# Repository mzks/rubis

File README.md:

# rubis

ADC board for 16 channels Slow Control on Raspberry pi.
This repository provides board design and control software.

## Demo
 - 30 seconds to start

 - Web watching demo

It is easy to watch your sensors with rubis + Grafana

 - PCB view on Raspbery Pi

## Feature

 - Standalone
 - Inexpensive
 - Multi channels (16 ch) and additional connectors (4 ch)
 - Including CLI software (This!)

## Hardware components
 - rubis board - less than 5 dollars at elecrow 
 - Raspberry Pi (1B+, 2B, 3B, 3B+, 4B, Zero)
 - [PIN Socket](https://akizukidenshi.com/catalog/g/gC-00085/) 
 - [ADC Board](https://www.marutsu.co.jp/pc/i/574270/) * 1--4 / 20 dollers per board
 - [BNC Connector](https://akizukidenshi.com/catalog/g/gC-00134/) ( * 4, optional)
 - [SMA Connector](https://akizukidenshi.com/catalog/g/gC-02569/) ( * 4, optional)
 - LEMO Connector (Optional)

## Hardware

You need to connect the four GPIO pins arranged in a square (Pin 3 -- SDA, Pin 4 -- 5V, Pin 5 -- SCL, Pin 6 -- GND).
 - [Circuit diagram](https://github.com/mzks/rubis/blob/main/hardware/rubis_circuit.pdf)
 - [3D view](https://github.com/mzks/rubis/blob/main/hardware/rubis.step)
 - [KiCad files](https://github.com/mzks/rubis/blob/main/hardware)

## Software

### Install
Before run, enable I2C on Raspberry Pi. (`sudo raspi-config`)
Then, you can find the i2c devices like this.
```
> sudo i2cdetect -y 1
     0  1  2  3  4  5  6  7  8  9  a  b  c  d  e  f
00:          -- -- -- -- -- -- -- -- -- -- -- -- --
10: -- -- -- -- -- -- -- -- -- -- -- -- -- -- -- --
20: -- -- -- -- -- -- -- -- -- -- -- -- -- -- -- --
30: -- -- -- -- -- -- -- -- -- -- -- -- -- -- -- --
40: -- -- -- -- -- -- -- -- 48 49 4a 4b -- -- -- --
50: -- -- -- -- -- -- -- -- -- -- -- -- -- -- -- --
60: -- -- -- -- -- -- -- -- -- -- -- -- -- -- -- --
70: -- -- -- -- -- -- -- --
```
If you will use an old raspberry pi, run `sudo apt install libatlas-base-dev` to use `numpy` (This tool doesn't depend on `numpy`).

Then, type `pip3 install rubis`
The `rubis` binary will be provided at `~/.local/bin/rubis`
You want mysql store, please see `Database setting` below.

### Usage
When you execute `rubis` without option, logging immidiately starts with default configurations.
You can use your custom configuration file with `-c` option.

`rubis -g` generates template config file.
Edit them, then run `rubis -c custom_config.json`.
At the **strong** request of the author's supervisor, the following commands are available to people in CYGNUS (dark matter search experiment) without creating or editing a new configuration file.
```
rubis -c cygnus
```
In addition of `cygnus`, `one_board` and `mysql` configurations are pre-defined.

Some configurations can be overwrited with command line options.
`rubis -h` provides option descriptions.
The output file format is CSV/MySQL.

As a default, the csv files like `sc-20211029-75enrt.csv` are created.
The `75enrt` is a unique hash created by configurations.
The hash helps separation not to mix files taken with different configurations.
The CSV format is like that.
```
time,ch1,ch2,ch3,ch4,ch5,ch6,ch7,ch8,ch9,ch10,ch11,ch12,ch13,ch14,ch15,ch16
2021-10-29 00:49:50, 0.5481417, 0.5476417, 0.5483917, 0.5476417, 0.5432666, 0.5430166, 0.5441416, 0.5433916, 0.5486417, 0.5478917, 0.5482667, 0.5477667, 0.5441416, 0.5446416, 0.5440166, 0.5440166
2021-10-29 00:50:51, 0.5486417, 0.5483917, 0.5475167, 0.5476417, 0.5437666, 0.5435166, 0.5435166, 0.5436416, 0.5482667, 0.5483917, 0.5485167, 0.5481417, 0.5451416, 0.5451416, 0.5438916, 0.5437666
2021-10-29 00:51:51, 0.5480167, 0.5478917, 0.5480167, 0.5475167, 0.5432666, 0.5431416, 0.5430166, 0.5437666, 0.5482667, 0.5481417, 0.5481417, 0.5480167, 0.5445166, 0.5436416, 0.5443916, 0.5443916
2021-10-29 00:52:51, 0.5487667, 0.5481417, 0.5481417, 0.5481417, 0.5437666, 0.5437666, 0.5438916, 0.5435166, 0.5487667, 0.5482667, 0.5483917, 0.5478917, 0.5448916, 0.5440166, 0.5442666, 0.5438916
2021-10-29 00:53:52, 0.5482667, 0.5486417, 0.5476417, 0.5477667, 0.5438916, 0.5437666, 0.5432666, 0.5435166, 0.5487667, 0.5481417, 0.5481417, 0.5485167, 0.5445166, 0.5440166, 0.5441416, 0.5440166
2021-10-29 00:54:52, 0.5482667, 0.5478917, 0.5477667, 0.5478917, 0.5433916, 0.5430166, 0.5436416, 0.5438916, 0.5487667, 0.5487667, 0.5488918, 0.5478917, 0.5451416, 0.5447666, 0.5442666, 0.5441416
2021-10-29 00:55:53, 0.5487667, 0.5480167, 0.5478917, 0.5475167, 0.5441416, 0.5437666, 0.5435166, 0.5433916, 0.5487667, 0.5480167, 0.5483917, 0.5482667, 0.5452666, 0.5450166, 0.5448916, 0.5441416
2021-10-29 00:56:53, 0.5487667, 0.5483917, 0.5482667, 0.5481417, 0.5440166, 0.5438916, 0.5441416, 0.5443916, 0.5491418, 0.5487667, 0.5483917, 0.5482667, 0.5446416, 0.5442666, 0.5441416, 0.5445166
2021-10-29 00:57:54, 0.5478917, 0.5483917, 0.5480167, 0.5480167, 0.5441416, 0.5438916, 0.5440166, 0.5442666, 0.5491418, 0.5488918, 0.5488918, 0.5481417, 0.5450166, 0.5443916, 0.5441416, 0.5442666
```

The `-r` option makes "dry-run".
With the option, this rubis works on general system not raspberry pi even without ADS board.
It helps to know how rubis works.

The `-l` option show rubis log.
It helps to find the logfile place and configuration with hash.

If you miss a config to generate hash, `-b` option helps you.
`rubis -b g2hlpc` generates the config file run before.

The `-q` option kill all rubis processes.
With the `-s` option, rubis uses the stored cofiguration used in the previous run.

For analysis with pandas dataframe, it is easy to extract the csv files.
```
import pandas as pd
from glob import glob

hash_str = '75enrt'
df = [pd.read_csv(name, parse_dates=[0], index_col=0) for name in sorted(glob('./*'+hash_str+'.csv'))]
df = pd.concat(df)
```

### Config option

| Configure name      | Description                      | Option                                                          | Overwrite option |
| ------------------- | -------------------------------- | --------------------------------------------------------------- | ---------------- |
| `path`              | Path to store the data           | Default: "./"                                                   | -p               |
| `file_header`       | File header of generated file    | Default: "sc"                                                   | -f               |
| `naming`            | Naming style of file             | `'date_hash.csv'`, etc. Available keywords : 'head', 'date', 'id', 'hash', 'host' | -n               |
| `rubis_id`          | rubis id (string)                | Used to identify your rubis board                               | -i               |
| `time_interval_sec` | Data taking time interval (sec)  | Default: 10                                                     | -t               |
| `available_boards`  | List of available ADS1115 boards | Default: [1,2,3,4]                                              | -a               |
| `output`            | Output format                    | `"csv"`, `"db"`, or `"both"`                                    | -o               |
| `delimiter`         | Delimiter for csv output         | `","`, `" "`, `"space"`, etc.                                          | -d               |
| `commentout_string` | Strings to be added on the csv file header | default: ""                                           |                  |
| `time_format`       | Time column format               | "timestamp", "datetime" (default), or strftime format (for example, "%H:%M:%S") |  |
| `boards`            | Setting for each ADS1115 board   | `"gain"` option is available                                    |                  |
| `sources`           | Setting for each channels        |                                                                 |                  |

If you select `naming` including "date", a new file will be created day by day.

The sources should be set like,
```
"1":{
    "name": "ch1",
    "description": "channel 1",
    "type": "volt"
    },
"2":{
    "name": "ch2",
    "description": "channel 2",
    "type": "linear"
    "a": 2.0,
    "b": 1.2
    },
```
The `name` is used for csv header. For the `type`, `"volt"`, `"raw"`, `"millivolt"`, and `"linear"` are available.
`"linear"` returns the value `"a" * (volt) + "b"`. The "a" and "b" should be written in the config file, for each sources.

## Database setting
If you want database store, do like that additionaly
```
sudo apt install mariadb-server
sudo mysql -u root
MariaDB [(none)]> UPDATE mysql.user SET password=password('newpassword') WHERE User = 'root';
MariaDB [mysql]> UPDATE mysql.user SET plugin='' WHERE User='root';
MariaDB [mysql]> GRANT ALL PRIVILEGES ON *.* TO 'root'@'localhost' identified by 'newpassword' with grant option;
MariaDB [mysql]> exit
sudo systemctl restart mysql
```
You need an external access, please make a user.
```
CREATE USER 'rubis'@'10.37.%' IDENTIFIED BY 'password';
GRANT ALL ON *.* TO 'rubis'@'10.37.%';
FLUSH PRIVILEGES;
```
And comment out the `bind-address` line in `/etc/mysql/mariadb.conf.d/50-server.cnf`.
In addition, add `default_time_zone='+00:00'` at the bottom of the file.
Then run `sudo systemctl restart mysql`.

If you need static IP access, please edit `/etc/dhcpcd.conf` like this.
```
# Example static IP configuration:
interface eth0
static ip_address=***.***.***.***/** # your IP/mask
static routers=***.***.***.*** # your gateway
static domain_name_servers=***.***.***.*** ***.***.***.*** # your DNS
```

When you set `"db"` or `"both"` for `output` in config file, the following settings are required.
```
"db":{
    "login":{
        "host": "127.0.0.1",
        "port": 3306,
        "user": "root",
        "passwd": "newpassword",
        "autocommit": true},
    "name": "rubis"
    }
```

## For developers
Clone this repository on your machine, then run `make.sh`.
If you need something, please feel free to send a PR or ask me on issue.

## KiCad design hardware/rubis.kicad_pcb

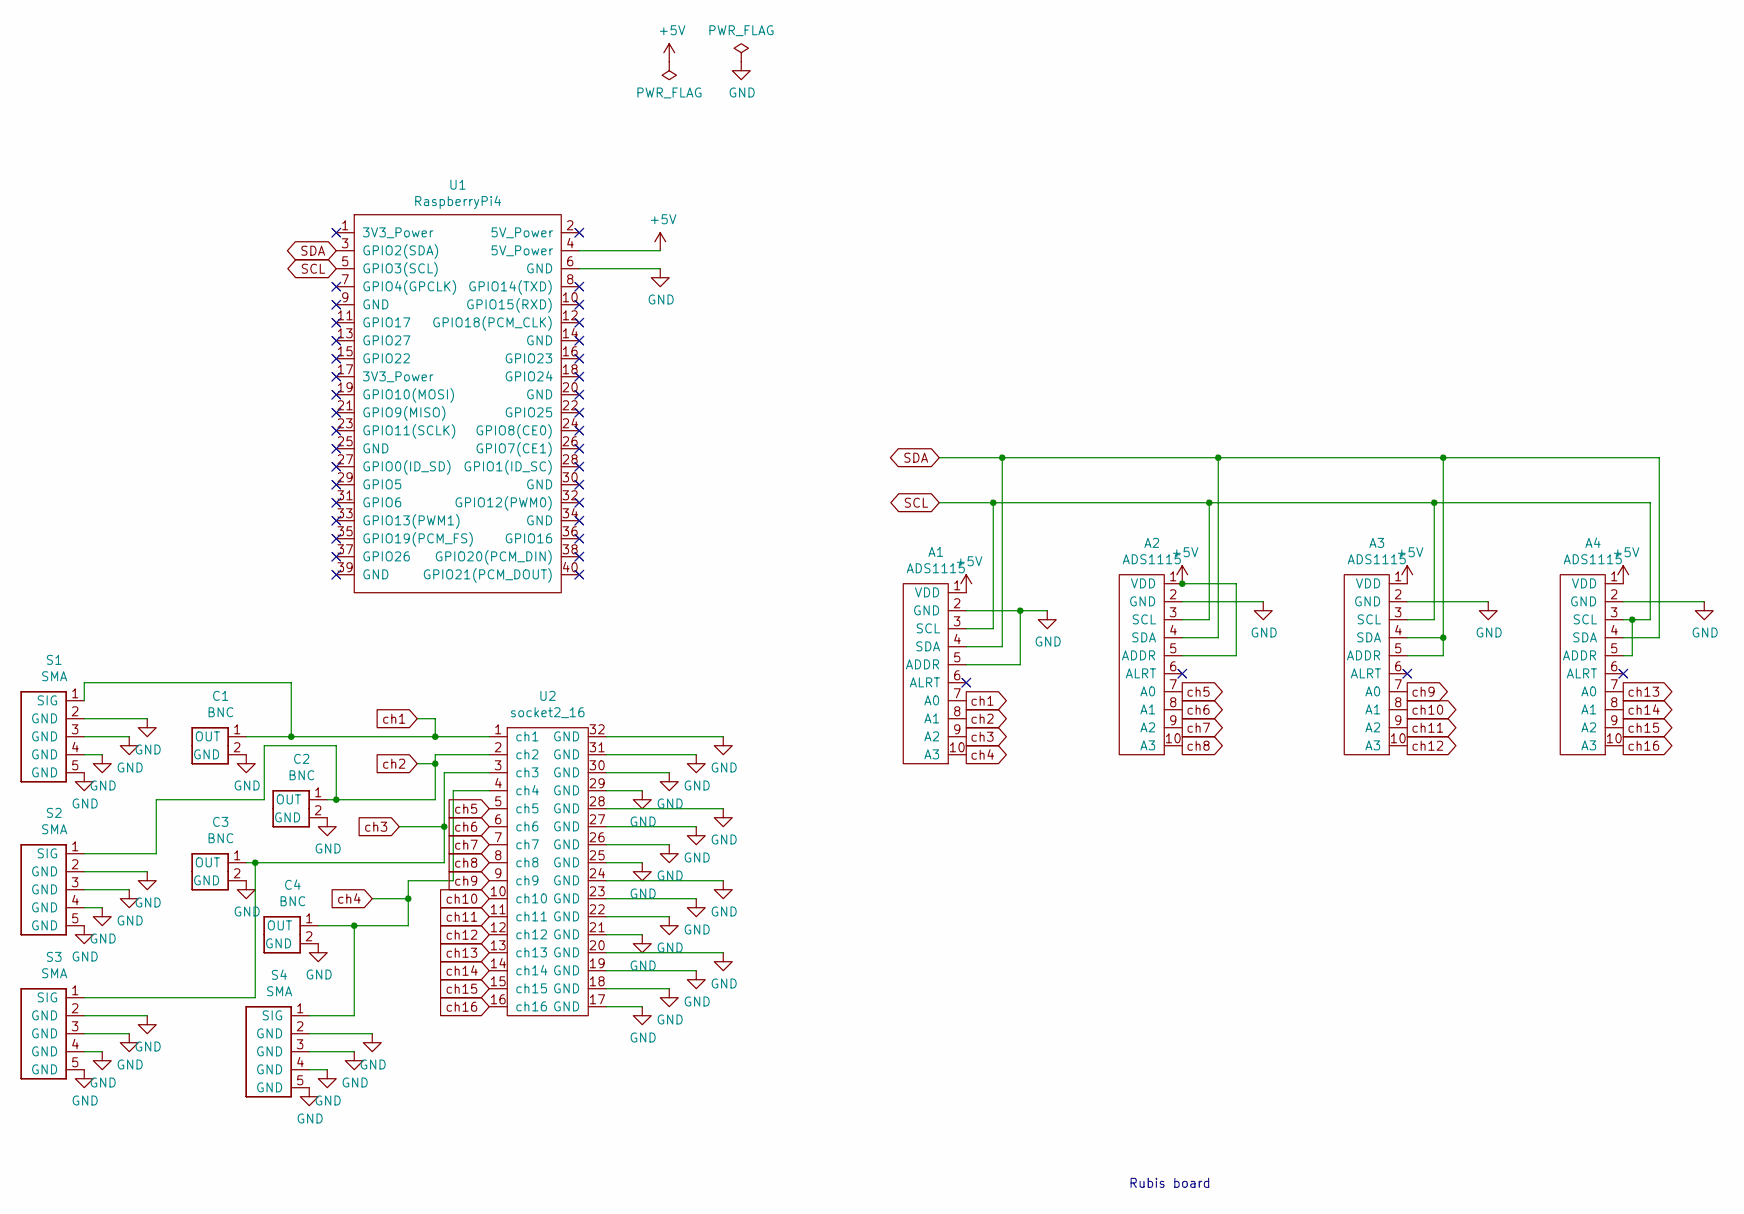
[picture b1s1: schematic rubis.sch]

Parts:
A1, A2, A3, A4: ADS1115; ads1115
C1, C2, C3, C4: BNC
S1, S2, S3, S4: SMA
U1: RaspberryPi4; rasp_40pin
U2: socket2_16; 2_16_socket

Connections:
+5V: A1.1 (VDD), A2.1 (VDD), A2.5 (ADDR), A3.1 (VDD), A4.1 (VDD), U1.4 (5V_Power); also elsewhere on the board
GND: A1.2 (GND), A1.5 (ADDR), A2.2 (GND), A3.2 (GND), A4.2 (GND), C1.2 (GND), C2.2 (GND), C3.2 (GND), C4.2 (GND), S1.2 (GND), S1.3 (GND), S1.4 (GND), S1.5 (GND), S2.2 (GND), S2.3 (GND), S2.4 (GND), S2.5 (GND), S3.2 (GND), S3.3 (GND), S3.4 (GND), S3.5 (GND), S4.2 (GND), S4.3 (GND), S4.4 (GND), S4.5 (GND), U1.6 (GND), U2.17 (GND), U2.18 (GND), U2.19 (GND), U2.20 (GND), U2.21 (GND), U2.22 (GND), U2.23 (GND), U2.24 (GND), U2.25 (GND), U2.26 (GND), U2.27 (GND), U2.28 (GND), U2.29 (GND), U2.30 (GND), U2.31 (GND), U2.32 (GND); also elsewhere on the board
SCL: A1.3 (SCL), A2.3 (SCL), A3.3 (SCL), A4.3 (SCL), A4.5 (ADDR), U1.5 (GPIO3(SCL)); also elsewhere on the board
SDA: A1.4 (SDA), A2.4 (SDA), A3.4 (SDA), A3.5 (ADDR), A4.4 (SDA), U1.3 (GPIO2(SDA)); also elsewhere on the board
ch1: A1.7 (A0), C1.1 (OUT), S1.1 (SIG), U2.1 (ch1); also elsewhere on the board
ch2: A1.8 (A1), C2.1 (OUT), S2.1 (SIG), U2.2 (ch2); also elsewhere on the board
ch3: A1.9 (A2), C3.1 (OUT), S3.1 (SIG), U2.3 (ch3); also elsewhere on the board
ch4: A1.10 (A3), C4.1 (OUT), S4.1 (SIG), U2.4 (ch4); also elsewhere on the board
ch5: A2.7 (A0), U2.5 (ch5)
ch6: A2.8 (A1), U2.6 (ch6)
ch7: A2.9 (A2), U2.7 (ch7)
ch8: A2.10 (A3), U2.8 (ch8)
ch9: A3.7 (A0), U2.9 (ch9)
ch10: A3.8 (A1), U2.10 (ch10)
ch11: A3.9 (A2), U2.11 (ch11)
ch12: A3.10 (A3), U2.12 (ch12)
ch13: A4.7 (A0), U2.13 (ch13)
ch14: A4.8 (A1), U2.14 (ch14)
ch15: A4.9 (A2), U2.15 (ch15)
ch16: A4.10 (A3), U2.16 (ch16)

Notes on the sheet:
Rubis board

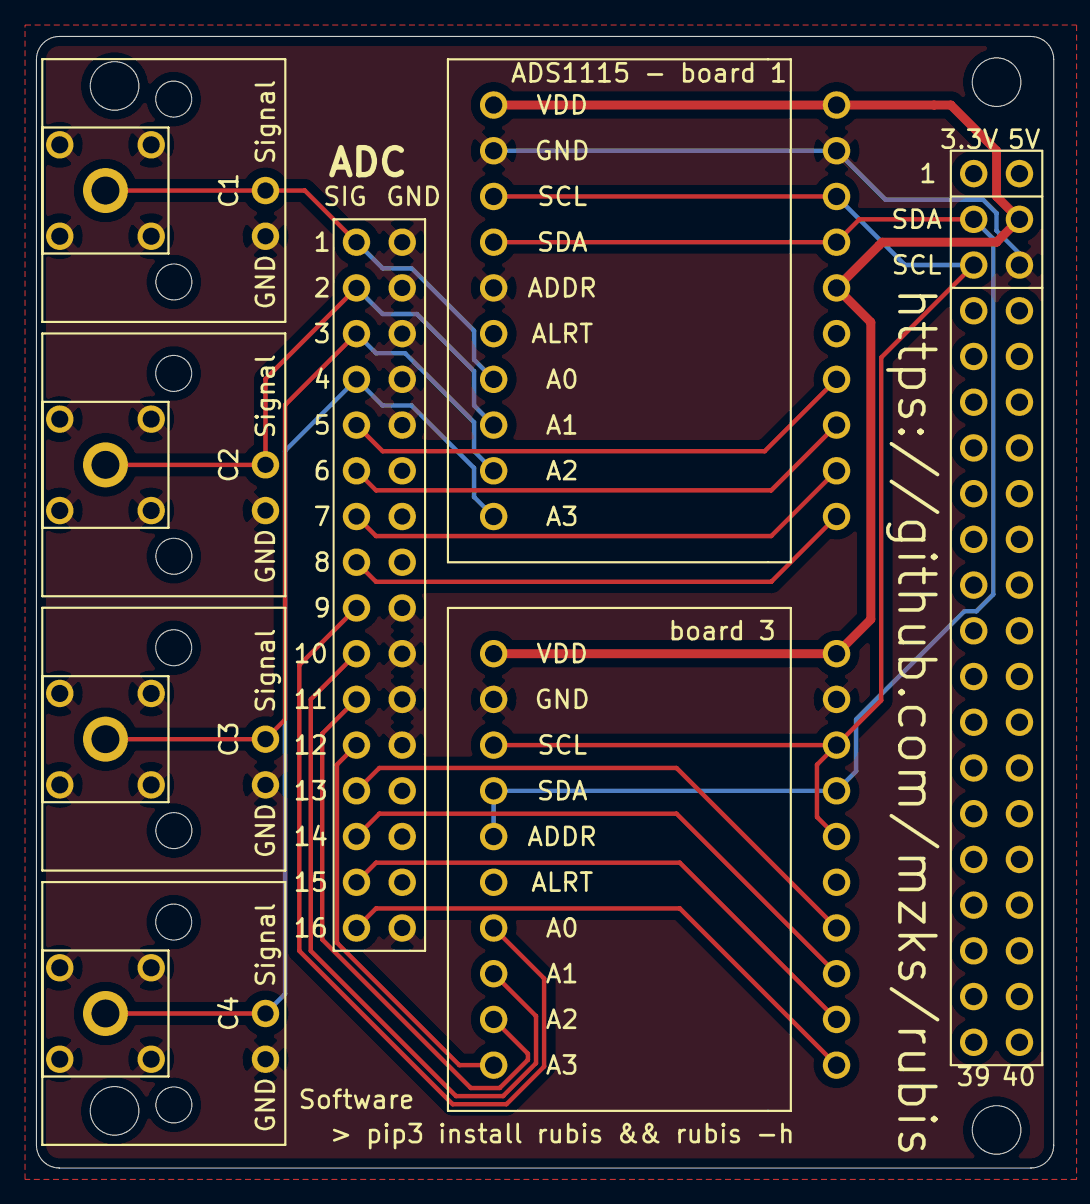
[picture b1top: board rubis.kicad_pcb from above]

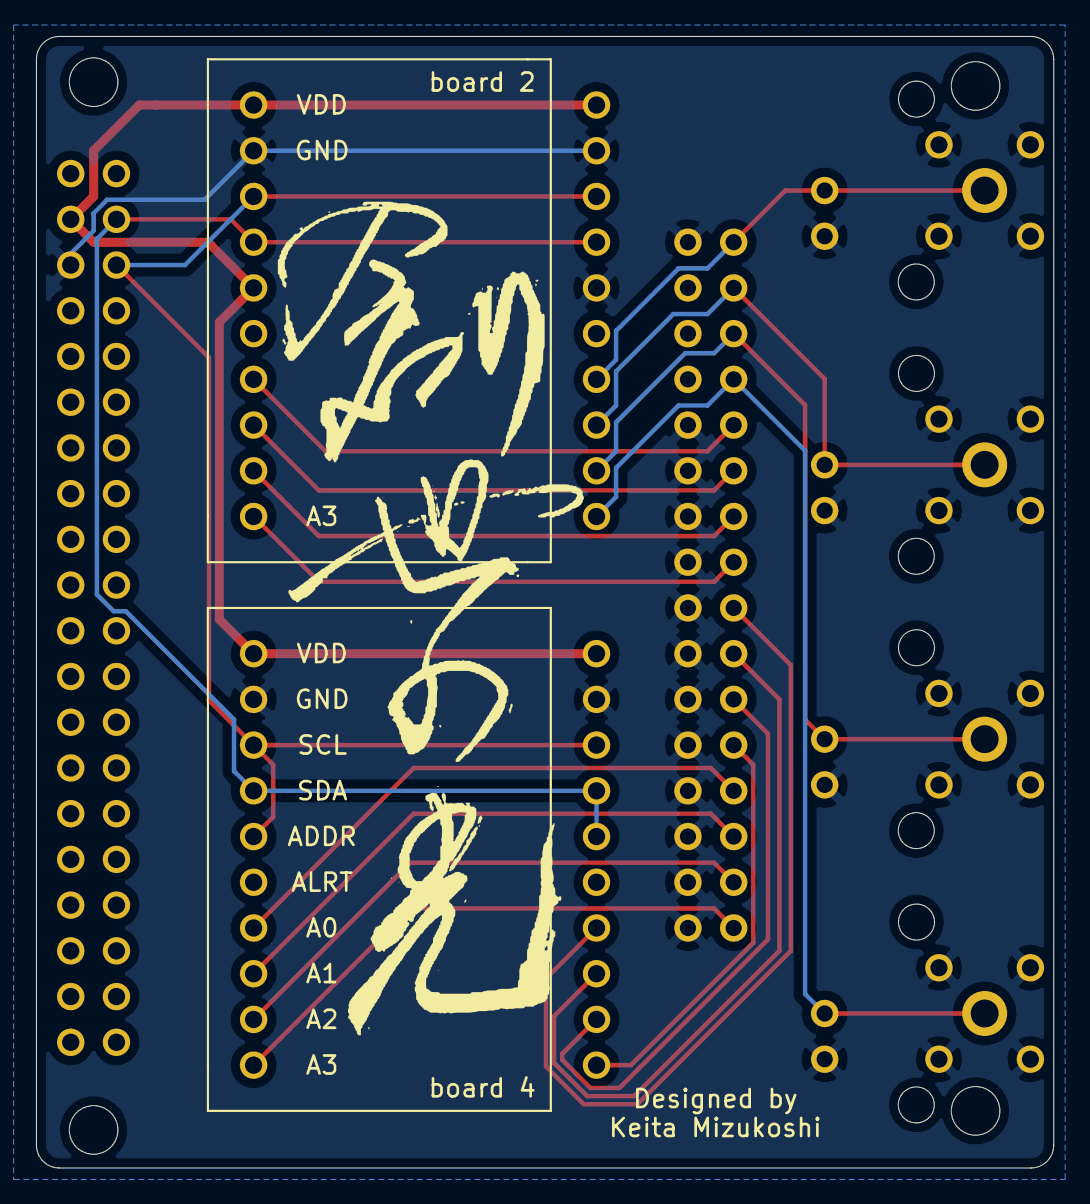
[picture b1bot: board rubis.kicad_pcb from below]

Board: 2 copper layers, 56.5 x 62.9 mm, 14 parts (2 on the bottom side), 20 nets.

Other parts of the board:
ADS1115 - board 1: ADS1115; ads1115

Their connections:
+5V: ADS1115 - board 1.1; also elsewhere on the board
GND: ADS1115 - board 1.2, ADS1115 - board 1.5; also elsewhere on the board
SCL: ADS1115 - board 1.3; also elsewhere on the board
SDA: ADS1115 - board 1.4; also elsewhere on the board
ch1: ADS1115 - board 1.7; also elsewhere on the board
ch2: ADS1115 - board 1.8; also elsewhere on the board
ch3: ADS1115 - board 1.9; also elsewhere on the board
ch4: ADS1115 - board 1.10; also elsewhere on the board

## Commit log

2021-09-24 Add info
2021-09-24 KiCAD files
2021-10-17 Add socket url
2021-10-20 Add initial software
2021-10-20 Upload board pictures
2021-10-20 Prepare for pypi
2021-10-20 Add options
2021-10-20 Documentation
2021-10-21 Add config generator
2021-10-21 Add type exception
2021-10-21 Add naming rule
2021-10-21 Add a bit
2021-10-21 bump version 0.1.1
2021-10-21 add import of shutil
2021-10-21 Remove config itself name
2021-10-21 Fix format
2021-10-21 Add documentation
2021-10-21 Add path option (fix)
2021-10-21 Add time_format option
2021-10-21 Bump version v0.1.3
2021-10-21 Print hash on console
2021-10-21 Change default style
2021-10-21 Fix float precision
2021-10-21 Add linear option and clean up
2021-10-21 Bump version 0.2.0
2021-10-21 Bug fix
2021-10-21 Initial db test
2021-10-21 Initial working
2021-10-21 Database store
2021-10-21 Add output format option
2021-10-21 Bump version 0.3.0
2021-10-23 Add insert datetime
2021-10-23 Change time type to timestamp
2021-10-28 Remove numpy dependence
2021-10-28 Add how to install
2021-10-28 Add description and fix output file format
2021-10-29 Remove pandas dependency
2021-11-05 allowed date for naming
2021-11-05 data path fixed
2021-11-10 path set fied, addd delimiter and commentout_char to configfile
2021-11-11 add CYGNUSconfig
2021-11-11 Refactor
2021-11-11 Test
2021-11-11 Readme update
2021-11-11 Change default file name option
2021-11-11 Add version option
2021-11-11 Fix import
2021-11-11 Bump version
2021-11-11 bug fix update
2021-11-11 Update readme for db setting
2021-11-11 update db info
2021-11-11 Add database setting
2021-11-11 Add unfunny jokes
2021-11-11 Add demo
2021-11-11 change a bit
2021-11-11 Bump version 0.5.0
2021-11-11 Add description of rubis_id option
2021-11-13 Add description for naming
2021-11-13 Add commentable-json
2021-11-13 Add comments to configuration file
2021-11-13 Update available boards option
2021-11-13 Version 0.6.0
2021-11-13 Modify CLI interface a bit
2021-11-13 indent fix
2021-11-19 Add circuit diagram in pdf
2021-11-21 Remove old hardware files
2021-11-21 Add hardware files for rubis 2
2021-11-21 Add 3D models
2021-11-22 Add gif demo
2021-11-23 Add pre-defined configurations
2021-11-23 Bump version 0.6.1
2021-11-24 Add dry run option
2021-11-24 jump to version 0.7
2021-11-24 Revert "Create python-publish.yml"
    This reverts commit aeca3e85013f05600b06fb56db14635e065eb410.
2021-11-24 Add test
2021-11-24 Add environment.yml for action
2021-11-24 Add GitHub action test
2021-11-24 Publish on GitHub
2021-11-24 Set theme jekyll-theme-minimal
2021-11-25 Add more test
2021-11-25 Add another configuration
2021-11-25 Add another test
2021-11-25 Use realistic dummy for dryrun
2021-11-26 Add quit option
2021-11-26 Add test for kill option
2021-11-26 Add kill option for README
2021-11-26 Add -s option
2021-11-26 Jump to ver. 0.8
2021-11-27 not kill itself
2021-11-27 Allow float time_interval_sec
2021-11-27 Add naive logger
2021-11-27 Add another test for log
2021-11-27 Not to kill itself
2021-11-27 Update document a bit
2021-11-27 Jump to version 9
2021-11-29 small fix
2021-11-29 Release v1.0.0
2021-11-29 Add badges
2021-11-29 Update issue templates
2021-12-10 Change IP address format
2021-12-20 Save config to package.data
2021-12-20 option to find bookkeeping config
2021-12-20 Update description
    -b option
2021-12-23 version 1.0.1
